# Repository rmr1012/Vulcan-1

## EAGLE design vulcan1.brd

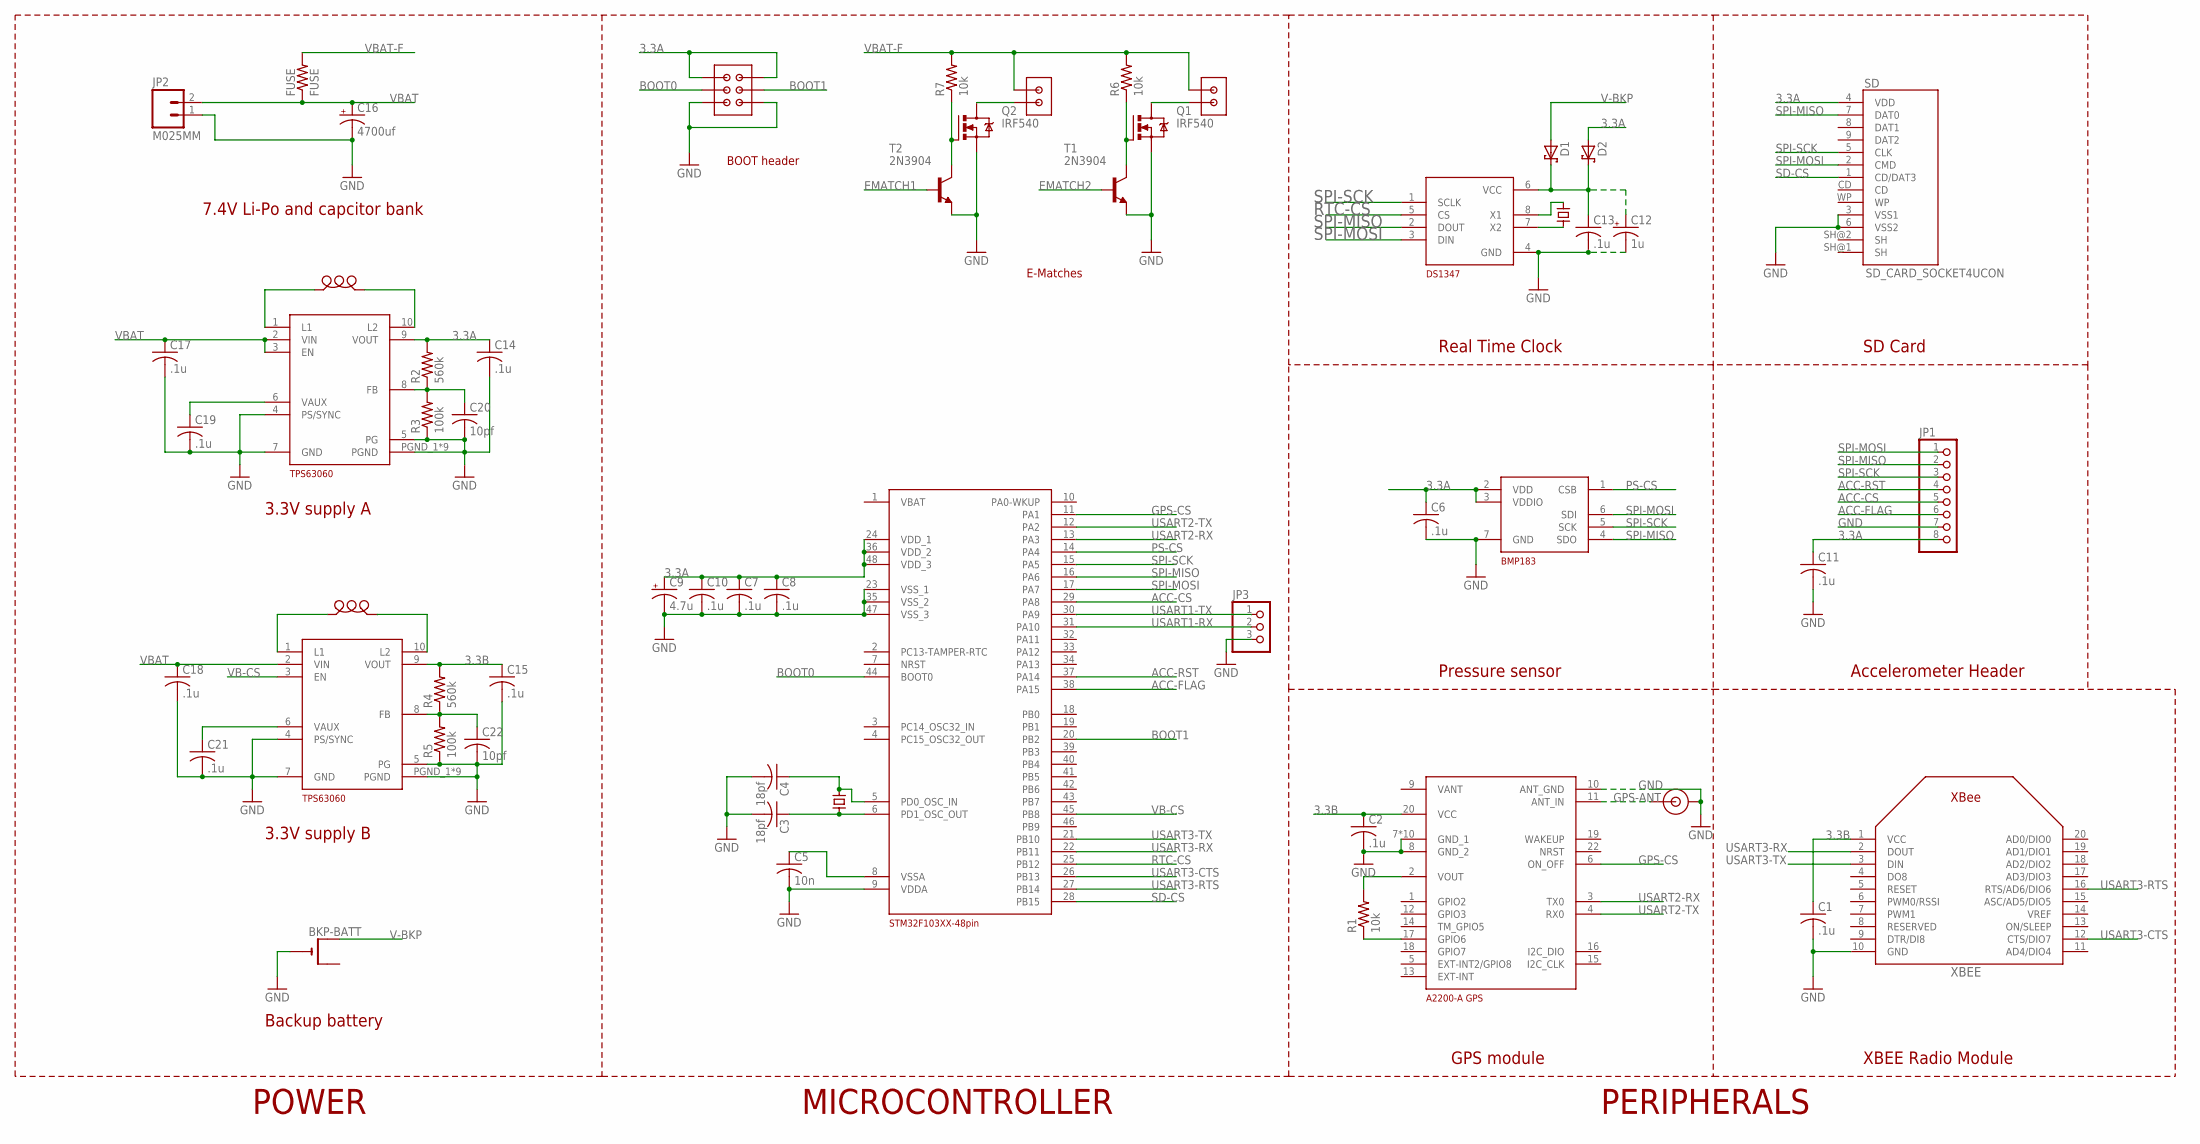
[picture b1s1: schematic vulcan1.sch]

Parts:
A2200-A: A2200-A; GPS-MODULE
BKP-BATT: CR1220THM; CR1220-THM
BMP1: BMP183; LGA-7
C1, C2, C6, C7, C8, C10, C11, C13, C14, C15, C17, C18, C19, C21: .1u; C025-030X050
C3, C4: 18pf; C025-030X050
C5: 10n; C025-030X050
C9: 4.7u; E2,5-6E
C12: 1u; E2,5-6E
C16: 4700uf; E5-13
C20, C22: 10pf; C025-030X050
D1, D2: SCHOTTKY-DIODEDO35-7; DO35-7
DS1: DS1347; TDFN-T822-2
FUSE: FUSE; 0204/7
JP1: PINHD-1X8CLEANBIG; 1X08-CLEANBIG
JP2: M025MM; SCREWTERMINAL-5MM-2
JP3: PINHD-1X3CB; 1X03-CLEANBIG
Q1, Q2: IRF540; TO220BV
R1, R6, R7: 10k; 0204/7
R2, R4: 560k; 0204/7
R3, R5: 100k; 0204/7
SD: SD_CARD_SOCKET4UCON; SDCARD_4UCONN
T1, T2: 2N3904; TO92
TPS63060-A, TPS63060-B: TPS63060; PWSON-N10
U$1: SMA
U$2: HC/49US(AT49); HC/49US
U$3: STM32F103XX-48PIN; LQFP48
U$4: ECX-306X
U$5, U$6: ASPI-0520LR; L-0520LR
U$7: 2X3
U$8, U$9: 1X2BIG
XBEE: XBEE

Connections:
3.3A: BMP1.2 (VDD), BMP1.3 (VDDIO), C6.1, C7.1, C8.1, C9.+, C10.1, C11.1, C14.1, D2.A, JP1.8, R2.2, SD.4 (VDD), TPS63060-A.9 (VOUT), U$3.24 (VDD_1), U$3.36 (VDD_2), U$3.48 (VDD_3), U$7.1, U$7.2
3.3B: A2200-A.20 (VCC), C1.1, C2.1, C15.1, R4.2, TPS63060-B.9 (VOUT), XBEE.1 (VCC)
ACC-CS: JP1.5, U$3.29 (PA8)
ACC-FLAG: JP1.6, U$3.38 (PA15)
ACC-RST: JP1.4, U$3.37 (PA14)
BOOT0: U$3.44 (BOOT0), U$7.3
BOOT1: U$3.20 (PB2), U$7.4
EMATCH1: T2.2 (B)
EMATCH2: T1.2 (B)
GND: A2200-A.7 (GND_1), A2200-A.8 (GND_2), A2200-A.10 (ANT_GND), A2200-A.P$1 (GND_1), A2200-A.P$2 (GND_1), A2200-A.P$3 (GND_1), A2200-A.P$4 (GND_1), A2200-A.P$5 (GND_1), A2200-A.P$6 (GND_1), A2200-A.P$7 (GND_1), A2200-A.P$8 (GND_1), A2200-A.P$9 (GND_1), BKP-BATT.-, BMP1.7 (GND), C1.2, C2.2, C3.2, C4.2, C5.2, C6.2, C7.2, C8.2, C9.-, C10.2, C11.2, C12.-, C13.2, C14.2, C15.2, C16.-, C17.2, C18.2, C19.2, C20.2, C21.2, C22.2, DS1.4 (GND), JP1.7, JP2.1, JP3.3, Q1.S, Q2.S, R3.1, R5.1, SD.3 (VSS1), SD.6 (VSS2), T1.3 (E), T2.3 (E), TPS63060-A.4 (PS/SYNC), TPS63060-A.5 (PG), TPS63060-A.7 (GND), TPS63060-A.PGND_1 (PGND), TPS63060-A.PGND_2 (PGND), TPS63060-A.PGND_3 (PGND), TPS63060-A.PGND_4 (PGND), TPS63060-A.PGND_5 (PGND), TPS63060-A.PGND_6 (PGND), TPS63060-A.PGND_7 (PGND), TPS63060-A.PGND_8 (PGND), TPS63060-A.PGND_9 (PGND), TPS63060-B.4 (PS/SYNC), TPS63060-B.5 (PG), TPS63060-B.7 (GND), TPS63060-B.PGND_1 (PGND), TPS63060-B.PGND_2 (PGND), TPS63060-B.PGND_3 (PGND), TPS63060-B.PGND_4 (PGND), TPS63060-B.PGND_5 (PGND), TPS63060-B.PGND_6 (PGND), TPS63060-B.PGND_7 (PGND), TPS63060-B.PGND_8 (PGND), TPS63060-B.PGND_9 (PGND), U$1.1 (OUT), U$1.2 (OUT), U$3.9 (VDDA), U$3.23 (VSS_1), U$3.35 (VSS_2), U$3.47 (VSS_3), U$7.5, U$7.6, XBEE.10 (GND)
GPS-ANT: A2200-A.11 (ANT_IN), U$1.3 (IN)
GPS-CS: A2200-A.6 (ON_OFF), U$3.11 (PA1)
unnamed: Q2.G, R7.1, T2.1 (C)
unnamed: C5.1, U$3.8 (VSSA)
unnamed: TPS63060-B.1 (L1), U$6.P$1
unnamed: TPS63060-B.10 (L2), U$6.P$2
unnamed: TPS63060-A.1 (L1), U$5.P$1
unnamed: TPS63060-A.10 (L2), U$5.P$2
unnamed: DS1.7 (X2), U$4.1
unnamed: DS1.8 (X1), U$4.4
unnamed: C3.1, U$2.1, U$3.6 (PD1_OSC_OUT)
unnamed: C4.1, U$2.2, U$3.5 (PD0_OSC_IN)
unnamed: C19.1, TPS63060-A.6 (VAUX)
unnamed: C12.+, C13.1, D1.C, D2.C, DS1.6 (VCC)
unnamed: Q2.D, U$9.2
unnamed: C20.1, R2.1, R3.2, TPS63060-A.8 (FB)
unnamed: C22.1, R4.1, R5.2, TPS63060-B.8 (FB)
unnamed: Q1.G, R6.1, T1.1 (C)
unnamed: Q1.D, U$8.2
unnamed: C21.1, TPS63060-B.6 (VAUX)
unnamed: A2200-A.2 (VOUT), R1.2
unnamed: A2200-A.17 (GPIO6), R1.1
PS-CS: BMP1.1 (CSB), U$3.14 (PA4)
RTC-CS: DS1.5 (CS), U$3.25 (PB12)
SD-CS: SD.1 (CD/DAT3), U$3.28 (PB15)
SPI-MISO: BMP1.4 (SDO), DS1.2 (DOUT), JP1.2, SD.7 (DAT0), U$3.16 (PA6)
SPI-MOSI: BMP1.6 (SDI), DS1.3 (DIN), JP1.1, SD.2 (CMD), U$3.17 (PA7)
SPI-SCK: BMP1.5 (SCK), DS1.1 (SCLK), JP1.3, SD.5 (CLK), U$3.15 (PA5)
USART1-RX: JP3.2, U$3.31 (PA10)
USART1-TX: JP3.1, U$3.30 (PA9)
USART2-RX: A2200-A.3 (TX0), U$3.13 (PA3)
USART2-TX: A2200-A.4 (RX0), U$3.12 (PA2)
USART3-CTS: U$3.26 (PB13), XBEE.12 (CTS/DIO7)
USART3-RTS: U$3.27 (PB14), XBEE.16 (RTS/AD6/DIO6)
USART3-RX: U$3.22 (PB11), XBEE.2 (DOUT)
USART3-TX: U$3.21 (PB10), XBEE.3 (DIN)
V-BKP: BKP-BATT.+1 (+), D1.A
VB-CS: TPS63060-B.3 (EN), U$3.45 (PB8)
VBAT: C16.+, C17.1, C18.1, FUSE.1, JP2.2, TPS63060-A.2 (VIN), TPS63060-A.3 (EN), TPS63060-B.2 (VIN)
VBAT-F: FUSE.2, R6.2, R7.2, U$8.1, U$9.1

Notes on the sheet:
POWER
Backup battery
3.3V supply B
3.3V supply A
7.4V Li-Po and capcitor bank
MICROCONTROLLER
PERIPHERALS
Real Time Clock
SD Card
Pressure sensor
GPS module
XBEE Radio Module
Accelerometer Header
E-Matches
BOOT header

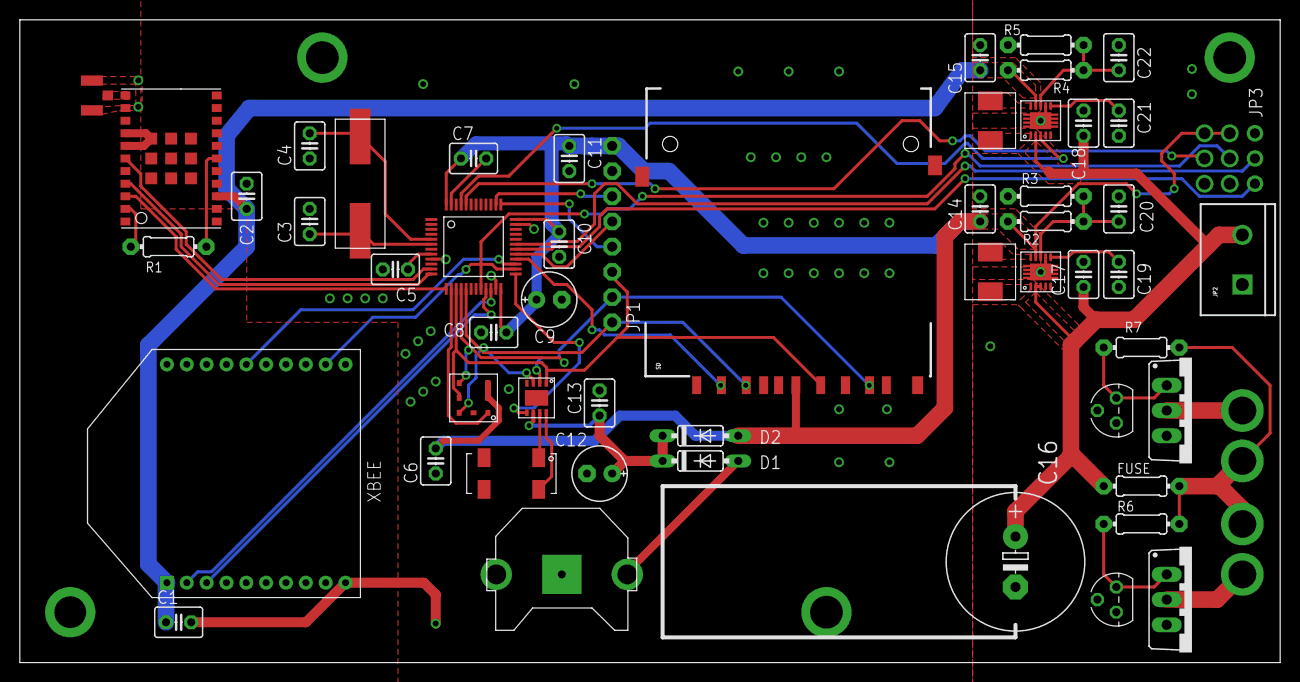
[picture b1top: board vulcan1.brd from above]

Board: 2 copper layers, 127.0 x 64.8 mm, 56 parts (0 on the bottom side), 48 nets.

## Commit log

2015-04-02 :space_invader: Added .gitattributes
2015-04-02 first upload
2015-04-02 Library filles
    all custom footprints
2015-04-05 library and schematic updates
2015-04-05 updates
    inductor, GPS, and DC converters added
2015-04-05 update
    thermocouple amp
2015-04-05 update
    crystal and RTC
2015-04-12 update-all but RF traces and gnd plane done
2015-04-13 update-gnd done
2015-04-15 Mounting holes placed
2015-04-15 Mounting holes placed, bad merge reverted
2015-04-15 Git error repaired
2015-04-21 labels cleaned up
2015-04-21 accelerometer reset and flag pins added
2015-04-21 added gnd vias to SMPS IC's
2015-05-05 final changes
2015-05-05 clearance changed to 8mil
2015-05-05 PCB submitted to vendor

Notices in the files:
parts and their libraries:
SparkFun-Connectors: Licensing: Creative Commons ShareAlike 4.0 International - https://creativecommons.org/licenses/by-sa/4.0
